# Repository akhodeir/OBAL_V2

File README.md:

# Welcome to the Pi-Fly Wiki

Welcome to the official Pi-Fly github page! 🚀

Pi-Fly is a next-generation automation platform designed to streamline and simplify the configuration of Raspberry Pi-based systems for Ardupilot, Pi Camera, and more. This platform takes advantage of modern Linux capabilities and offers an easy-to-use Python script to automatically configure your system for optimal performance.

Whether you're a developer, hobbyist, or a drone enthusiast, Pi-Fly is designed to help you easily set up and run your systems with minimal effort. Our goal is to provide you with the tools you need to succeed in your projects, whether it's automating flight controllers, working with IMUs, or streaming live video from your Pi Camera.

### Why Pi-Fly?  
- **64-bit Architecture** 🏎️ - Faster and more efficient than previous versions.  
- **Automated Setup** ⚙️ - No manual kernel tweaking; everything is configured via script.  
- **Multi-Sensor Support** 📡 - Works with multiple IMUs, GPS modules, and ADCs.  
- **AI & Computer Vision Ready** 🤖 - With the powerful Raspberry Pi 4, the **Pi Camera Module 3** can be leveraged for AI-based applications such as object detection, autonomous navigation, and real-time video analysis.  
- **Affordable & Open-Source** 💡 - A high-performance alternative to expensive, proprietary flight controllers.  

Feel free to explore the various setup guides, troubleshooting tips, and features that Pi-Fly offers. If you have any questions or suggestions, don't hesitate to reach out—we're here to help you make the most of your experience with Pi-Fly!

Check out the [Pi-Fly Wiki](https://github.com/akhodeir/Pi-Fly/wiki) for all the details.

**Note** : The board/project is not limited to Ardupilot. It can be used with any other flight controller such as PX4, INAV, Betaflight, your own flight controler,...etc
**Note**: : The initial name of the project was OBAL_V2, the name was changed to Pi-Fly due to some political issues with the owner of initial OBAL !!

Happy building! 🚁✨

# OBAL vs Pi-Fly vs Navio2 - Comparison

## 🚀 Overview
This table outlines the **significant improvements** made from the initial **OBAL** to **Pi-Fly** and compares it with the **Navio2** flight controller system.

---

## ⚙️ **Feature Comparison**

| Feature                | OBAL          | Pi-Fly        | Navio2             |
|------------------------|---------------|----------------|--------------------|
| **Linux Kernel**        | Bulleyes      | Bookworm       | Raspbian + ROS     |
| **Ardupilot**           | 32-bit        | 64-bit         | ?                  |
| **Linux Configuration** | Manual        | Automatic via script | Manual        |
| **Rx Protocol**         | PPM/PWM           | IBUS and SBUS  | PPM and SBUS       |
| **Flight Controller**   | Prototype     | Complete system| Complete system    |
| **IMU**                 | GY-91         | GY-91, GY-912, ... + more | MPU9250, LSM9DS1 |
| **Display**             | No            | Yes            | No                 |
| **Power Module**        | No            | Yes            | Yes                |
| **License**             | Open source   | Open source    | Proprietary        |
| **Price**               | < $60         | < $60          | $199               |
| **Link**                | [here](https://github.com/HefnySco/OBAL)     | [here](#)      | [here](https://navio2.hipi.io/)        |

---

## ⚠️ **Cons with Initial OBAL:**
- Uses **analog Rx protocol (PPM) or (PWM)**, limiting flexibility.
- Limited to **GY-91 IMU** (only possible IMU).
- **Safety switch** is not well designed.
- No proper **logic conversion** (mix of **5V and 3.3V** logical levels with Raspberry Pi).
- Uses an **old Linux version**, requiring recompilation to disable **`CONFIG_STRICT_DEVMEM`**.
- **32-bit Ardupilot** applications limit performance.

---
## [Donation] Your support is invaluable to this project!

Countless hours of hard work, prototyping, and investment in tools and materials have gone into making this project a reality. If you appreciate the effort and would like to contribute, your donation will help us continue developing and improving Pi-Fly.

Please consider donating for the project. There were tremendous effort added in this project. 
Many prototype boards were built and a lot of tools were purchased to make this project become true.

click image below to start donating :

[

](https://www.paypal.com/donate/?hosted_button_id=LGAC3VKW2A8ZA)

**Important**

Use this project at your own risk.

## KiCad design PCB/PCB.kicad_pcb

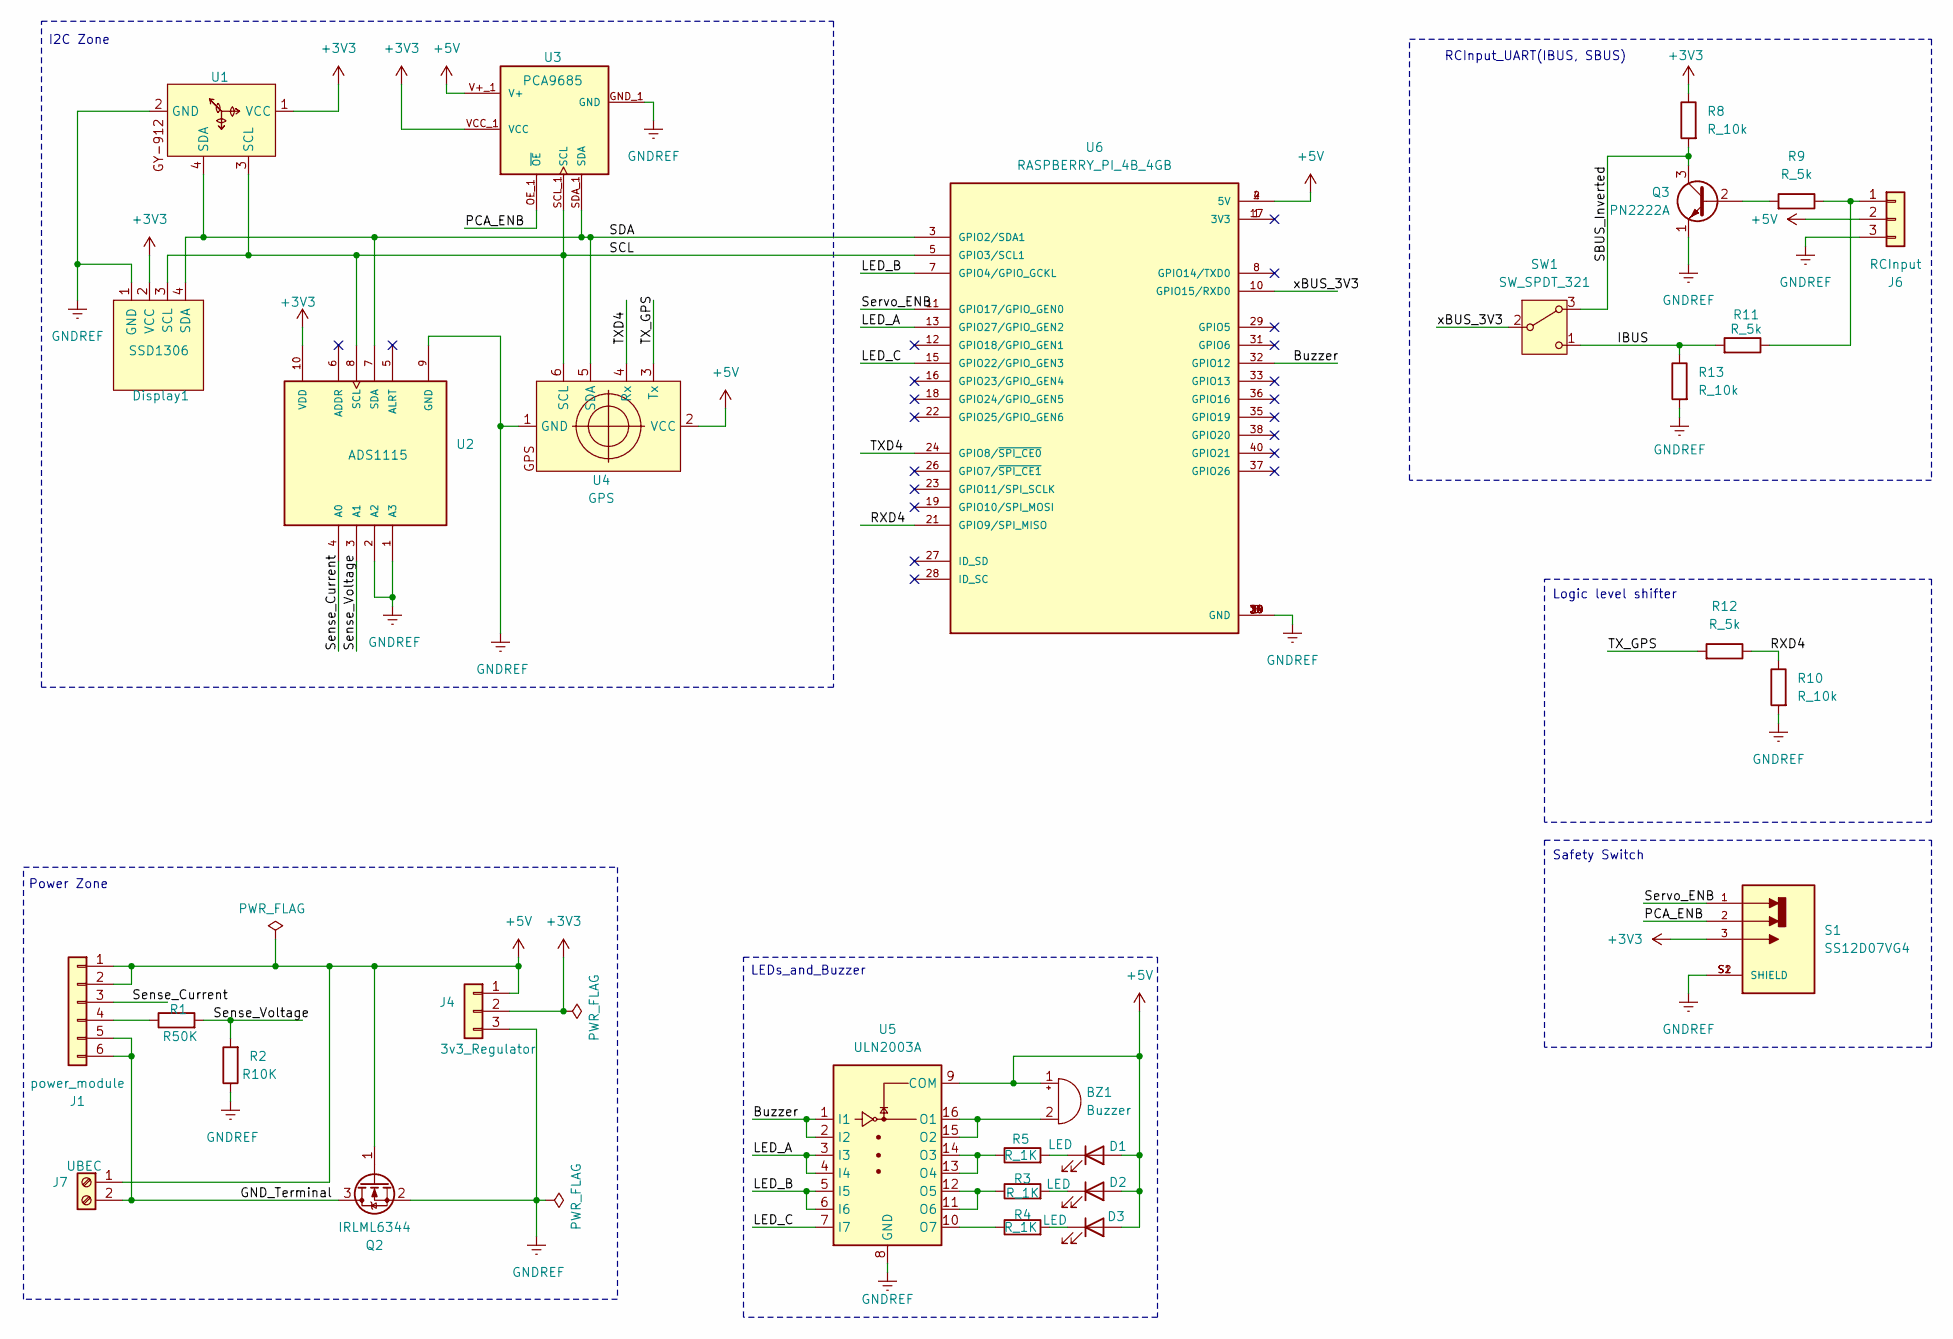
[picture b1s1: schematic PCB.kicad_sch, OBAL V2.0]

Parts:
BZ1: Buzzer; Buzzer_12x9.5RM7.6
D1, D2, D3: LED; LED_D3.0mm
Display1: SSD1306
J1: power_module
J4: 3v3_Regulator; Regulator
J6: RCInput; RCInput_xBUS
J7: UBEC; PinHeader_1x02_P2.54mm_Vertical
Q2: IRLML6344; SOT-23
Q3: PN2222A; TO-92_Inline_Wide
R1: R50K; R_Axial_DIN0207_L6.3mm_D2.5mm_P7.62mm_Horizontal
R2: R10K; R_Axial_DIN0207_L6.3mm_D2.5mm_P7.62mm_Horizontal
R3, R4, R5: R_1K; R_Axial_DIN0207_L6.3mm_D2.5mm_P7.62mm_Horizontal
R8, R10, R13: R_10k; R_Axial_DIN0207_L6.3mm_D2.5mm_P7.62mm_Horizontal
R9, R11, R12: R_5k; R_Axial_DIN0207_L6.3mm_D2.5mm_P7.62mm_Horizontal
S1: SS12D07VG4; SW_SS12D07VG4; PARTREV 1
SW1: SW_SPDT_321; xBUS_Selector
U1: GY-912
U2: ADS1115; MODULE_ADS1115; PARTREV N/A
U3: PCA9685; MODULE_815; PARTREV C
U4: GPS; GPS_SH1.0
U5: ULN2003A; DIP-16_W7.62mm_LongPads
U6: RASPBERRY_PI_4B_4GB; RPI_4_Hat_B+; PARTREV 4

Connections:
+3V3: Display1.2 (VCC), J4.2, R8.1, S1.3, U1.1 (VCC), U2.10 (VDD), U3.VCC_1 (VCC)
+5V: BZ1.1 (+), D1.2 (A), D2.2 (A), D3.2 (A), J1.1, J1.2, J4.1, J6.2, J7.1, Q2.1 (G), U3.V+_1 (V+), U4.2 (VCC), U5.9 (COM), U6.2 (5V), U6.4 (5V)
/Buzzer: U5.1 (I1), U5.2 (I2), U6.32 (GPIO12)
/GND_Terminal: J1.5, J1.6, J7.2, Q2.3 (S)
/IBUS: R11.2, R13.1, SW1.1 (C)
/LED_A: U5.3 (I3), U5.4 (I4), U6.13 (GPIO27/GPIO_GEN2)
/LED_B: U5.5 (I5), U5.6 (I6), U6.7 (GPIO4/GPIO_GCKL)
/LED_C: U5.7 (I7), U6.15 (GPIO22/GPIO_GEN3)
/PCA_ENB: S1.2, U3.OE_1 (~OE)
/RXD4: R10.1, R12.1, U6.21 (GPIO9/SPI_MISO)
/SBUS_Inverted: Q3.3 (C), R8.2, SW1.3 (A)
/SCL: Display1.3 (SCL), U1.3 (SCL), U2.8 (SCL), U3.SCL_1 (SCL), U4.6 (SCL), U6.5 (GPIO3/SCL1)
/SDA: Display1.4 (SDA), U1.4 (SDA), U2.7 (SDA), U3.SDA_1 (SDA), U4.5 (SDA), U6.3 (GPIO2/SDA1)
/Sense_Current: J1.3, U2.4 (A0)
/Sense_Voltage: R1.2, R2.2, U2.3 (A1)
/Servo_ENB: S1.1, U6.11 (GPIO17/GPIO_GEN0)
/TXD4: U4.4 (Rx), U6.24 (GPIO8/~SPI_CE0)
/TX_GPS: R12.2, U4.3 (Tx)
/xBUS_3V3: SW1.2 (B), U6.10 (GPIO15/RXD0)
GNDREF: Display1.1 (GND), J4.3, J6.3, Q2.2 (D), Q3.1 (E), R2.1, R10.2, R13.2, S1.S1 (SHIELD), S1.S2 (SHIELD), U1.2 (GND), U2.1 (A3), U2.2 (A2), U2.9 (GND), U3.GND_1 (GND), U4.1 (GND), U5.8 (GND), U6.6 (GND), U6.9 (GND), U6.14 (GND), U6.20 (GND), U6.25 (GND), U6.30 (GND), U6.34 (GND), U6.39 (GND)
unnamed: BZ1.2 (-), U5.15 (O2), U5.16 (O1)
unnamed: D1.1 (K), R5.2
unnamed: D2.1 (K), R3.2
unnamed: D3.1 (K), R4.2
unnamed: J1.4, R1.1
unnamed: J6.1, R9.1, R11.1
unnamed: Q3.2 (B), R9.2
unnamed: R5.1, U5.13 (O4), U5.14 (O3)
unnamed: R3.1, U5.11 (O6), U5.12 (O5)
unnamed: R4.1, U5.10 (O7)

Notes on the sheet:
I2C Zone
Power Zone
LEDs_and_Buzzer
Safety Switch
Logic level shifter
RCInput_UART(IBUS, SBUS)

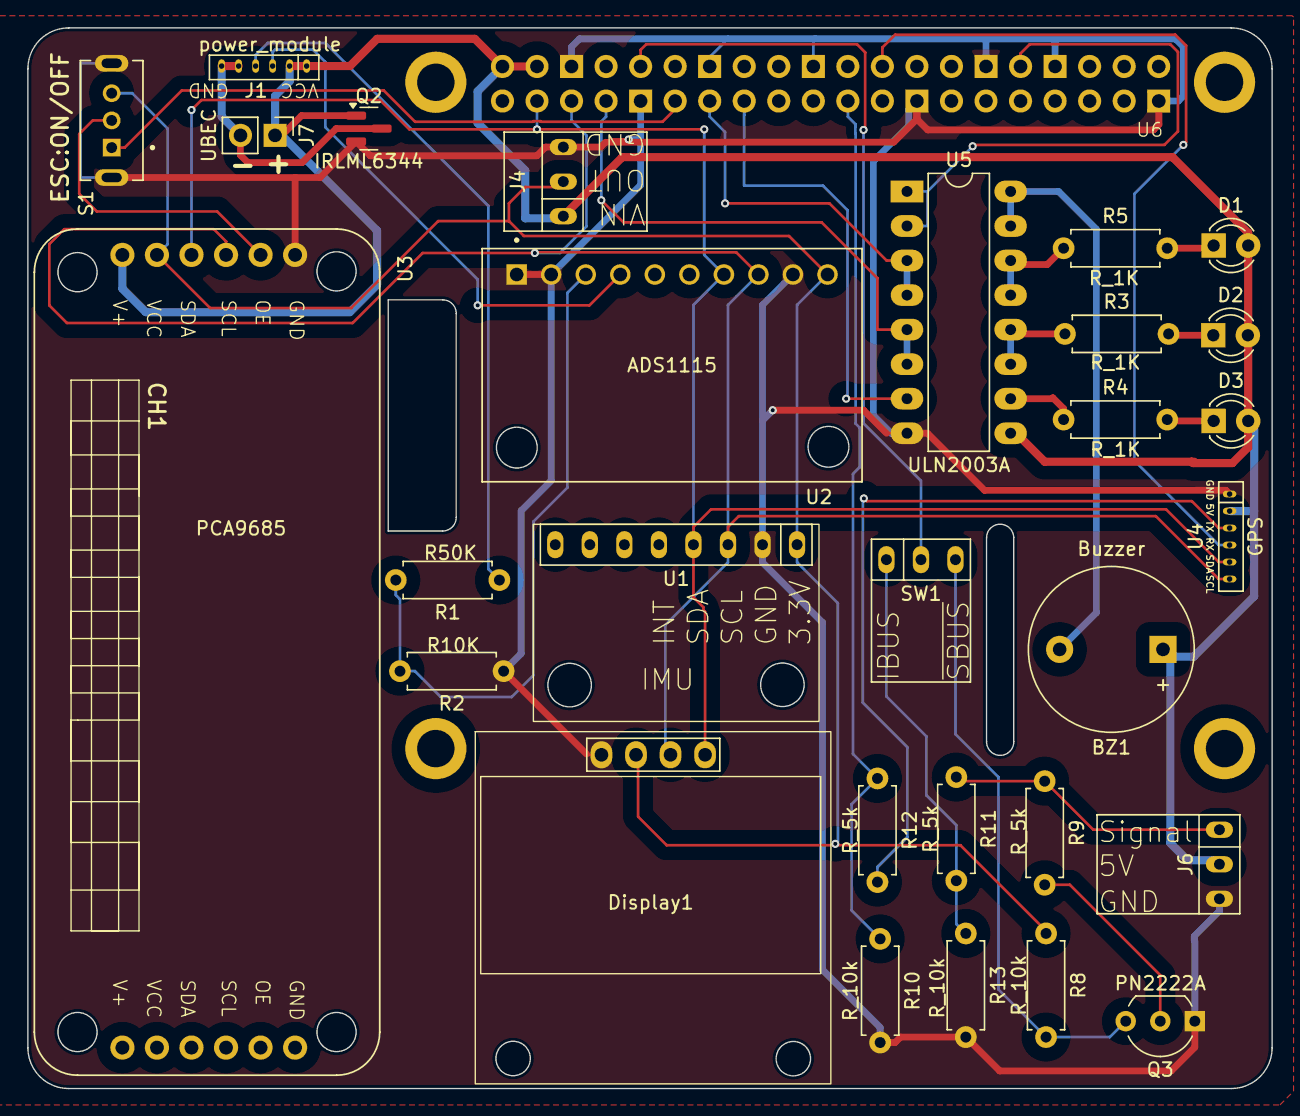
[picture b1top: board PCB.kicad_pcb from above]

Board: 2 copper layers, 91.5 x 78.0 mm, 30 parts (0 on the bottom side), 30 nets.

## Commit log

2025-03-03 Create required
2025-03-03 Rename paypal-donate-button.png to photo/paypal-donate-button.png
2025-03-29 Create Scripts
2025-03-29 Create myscript
2025-03-29 add PCB files
